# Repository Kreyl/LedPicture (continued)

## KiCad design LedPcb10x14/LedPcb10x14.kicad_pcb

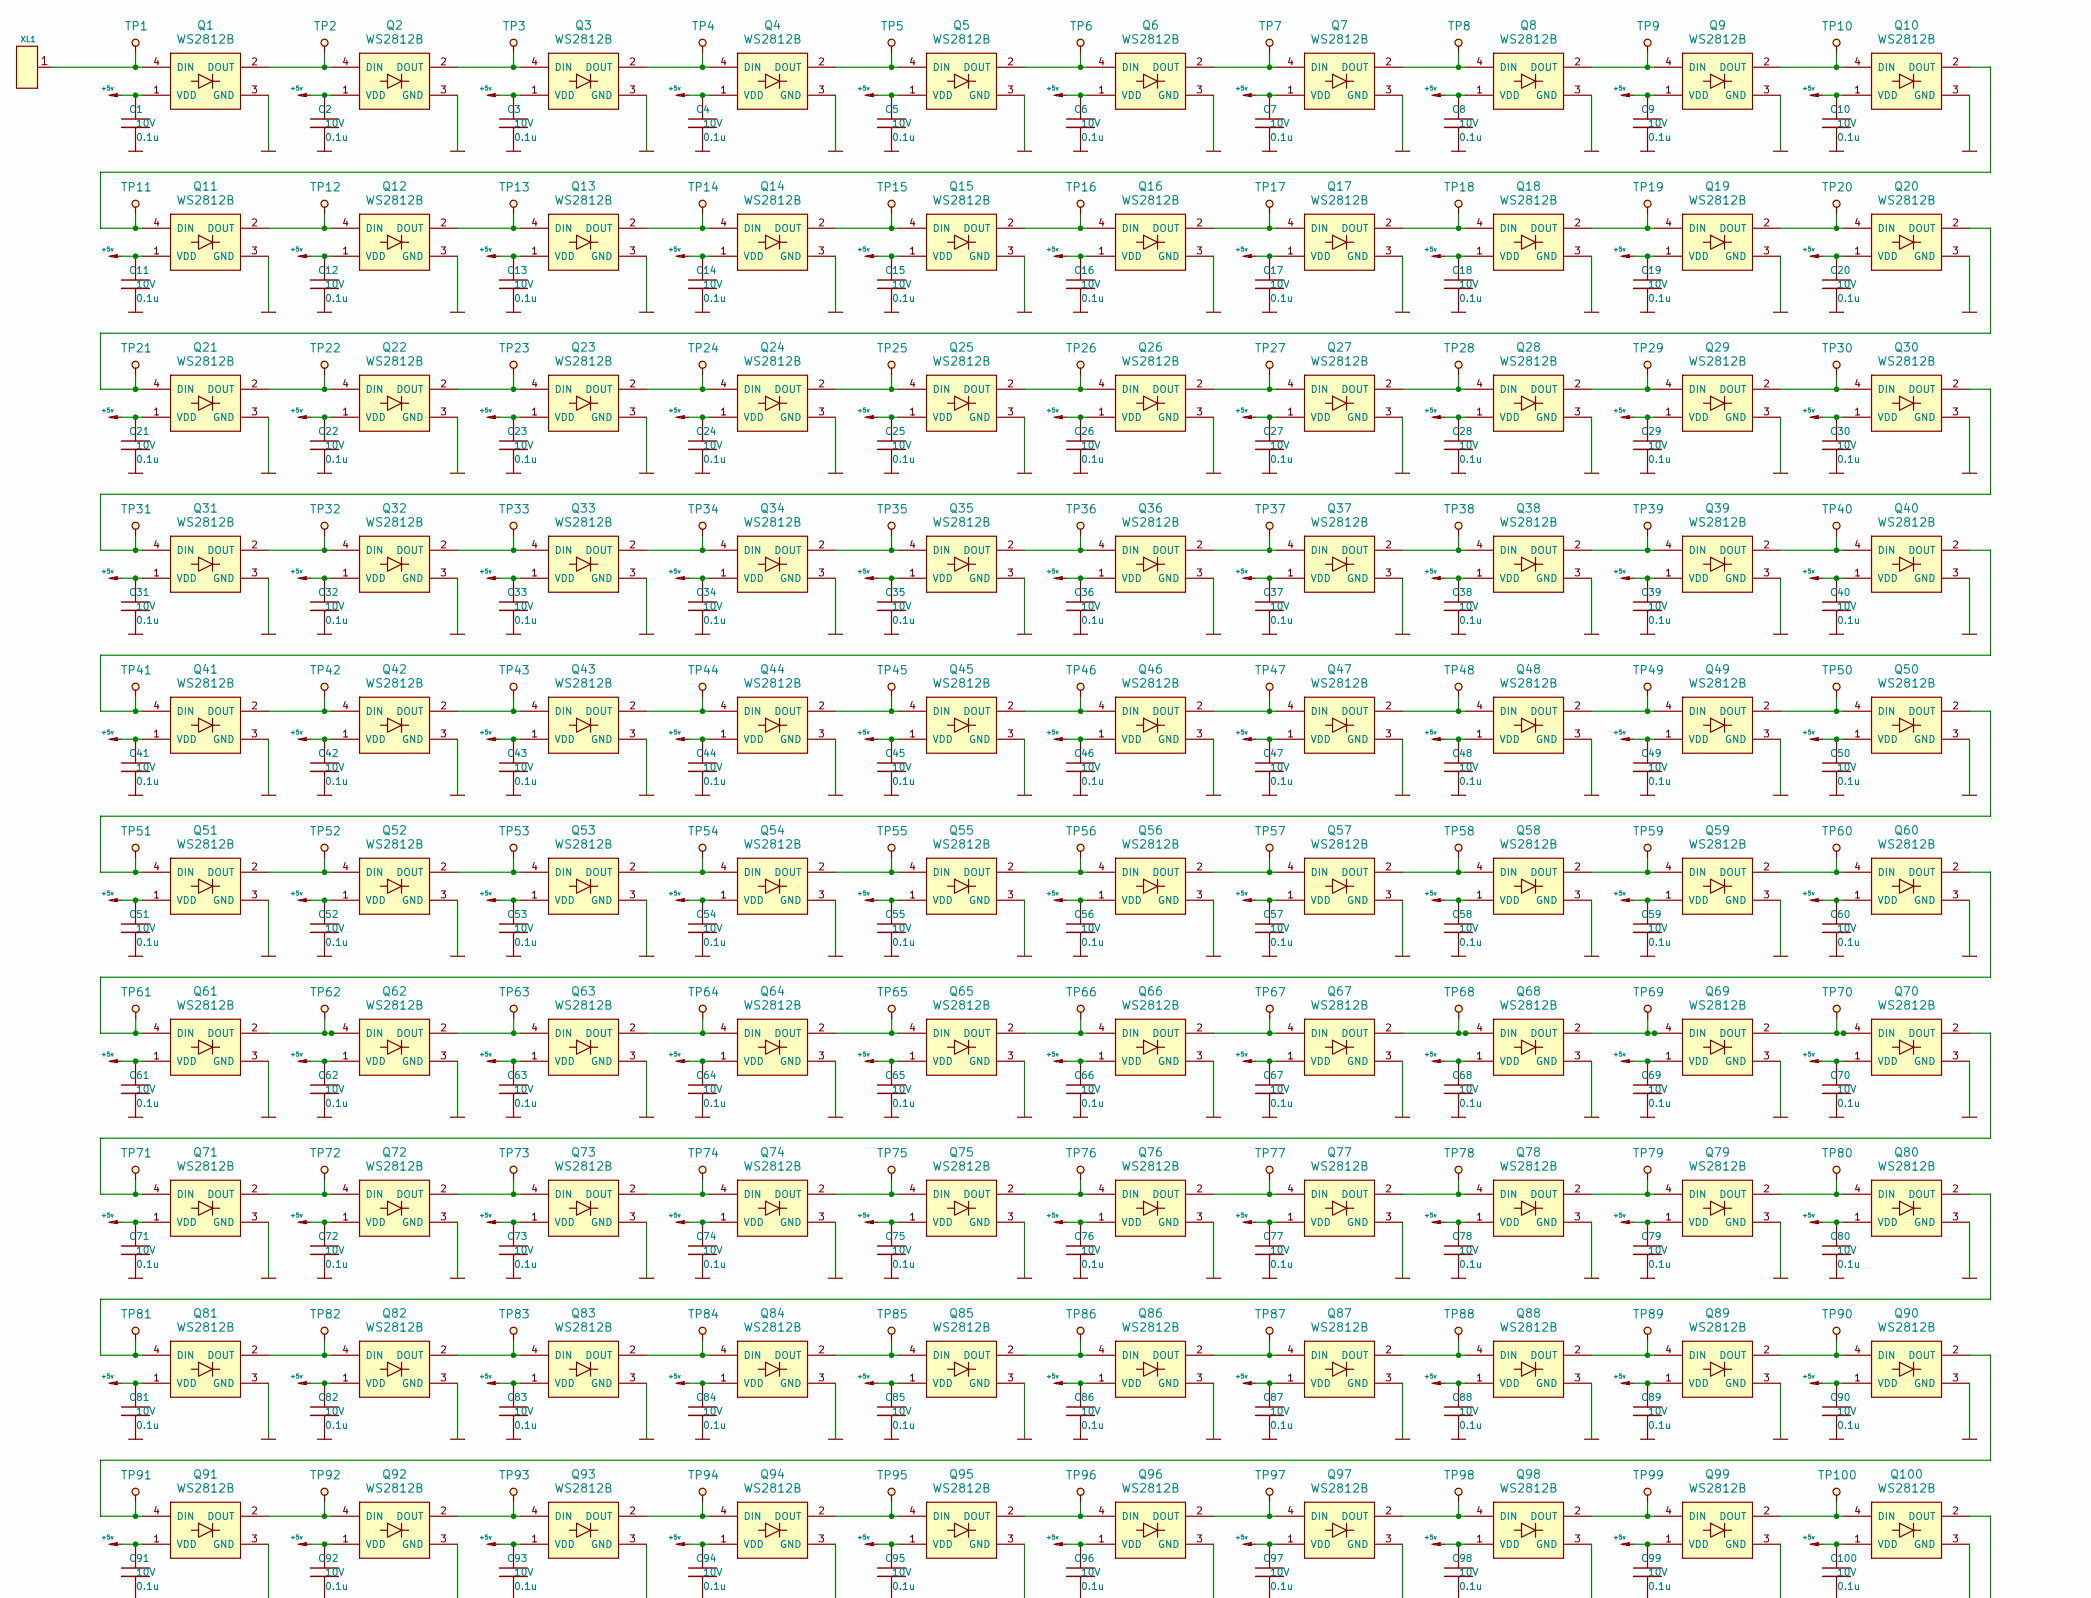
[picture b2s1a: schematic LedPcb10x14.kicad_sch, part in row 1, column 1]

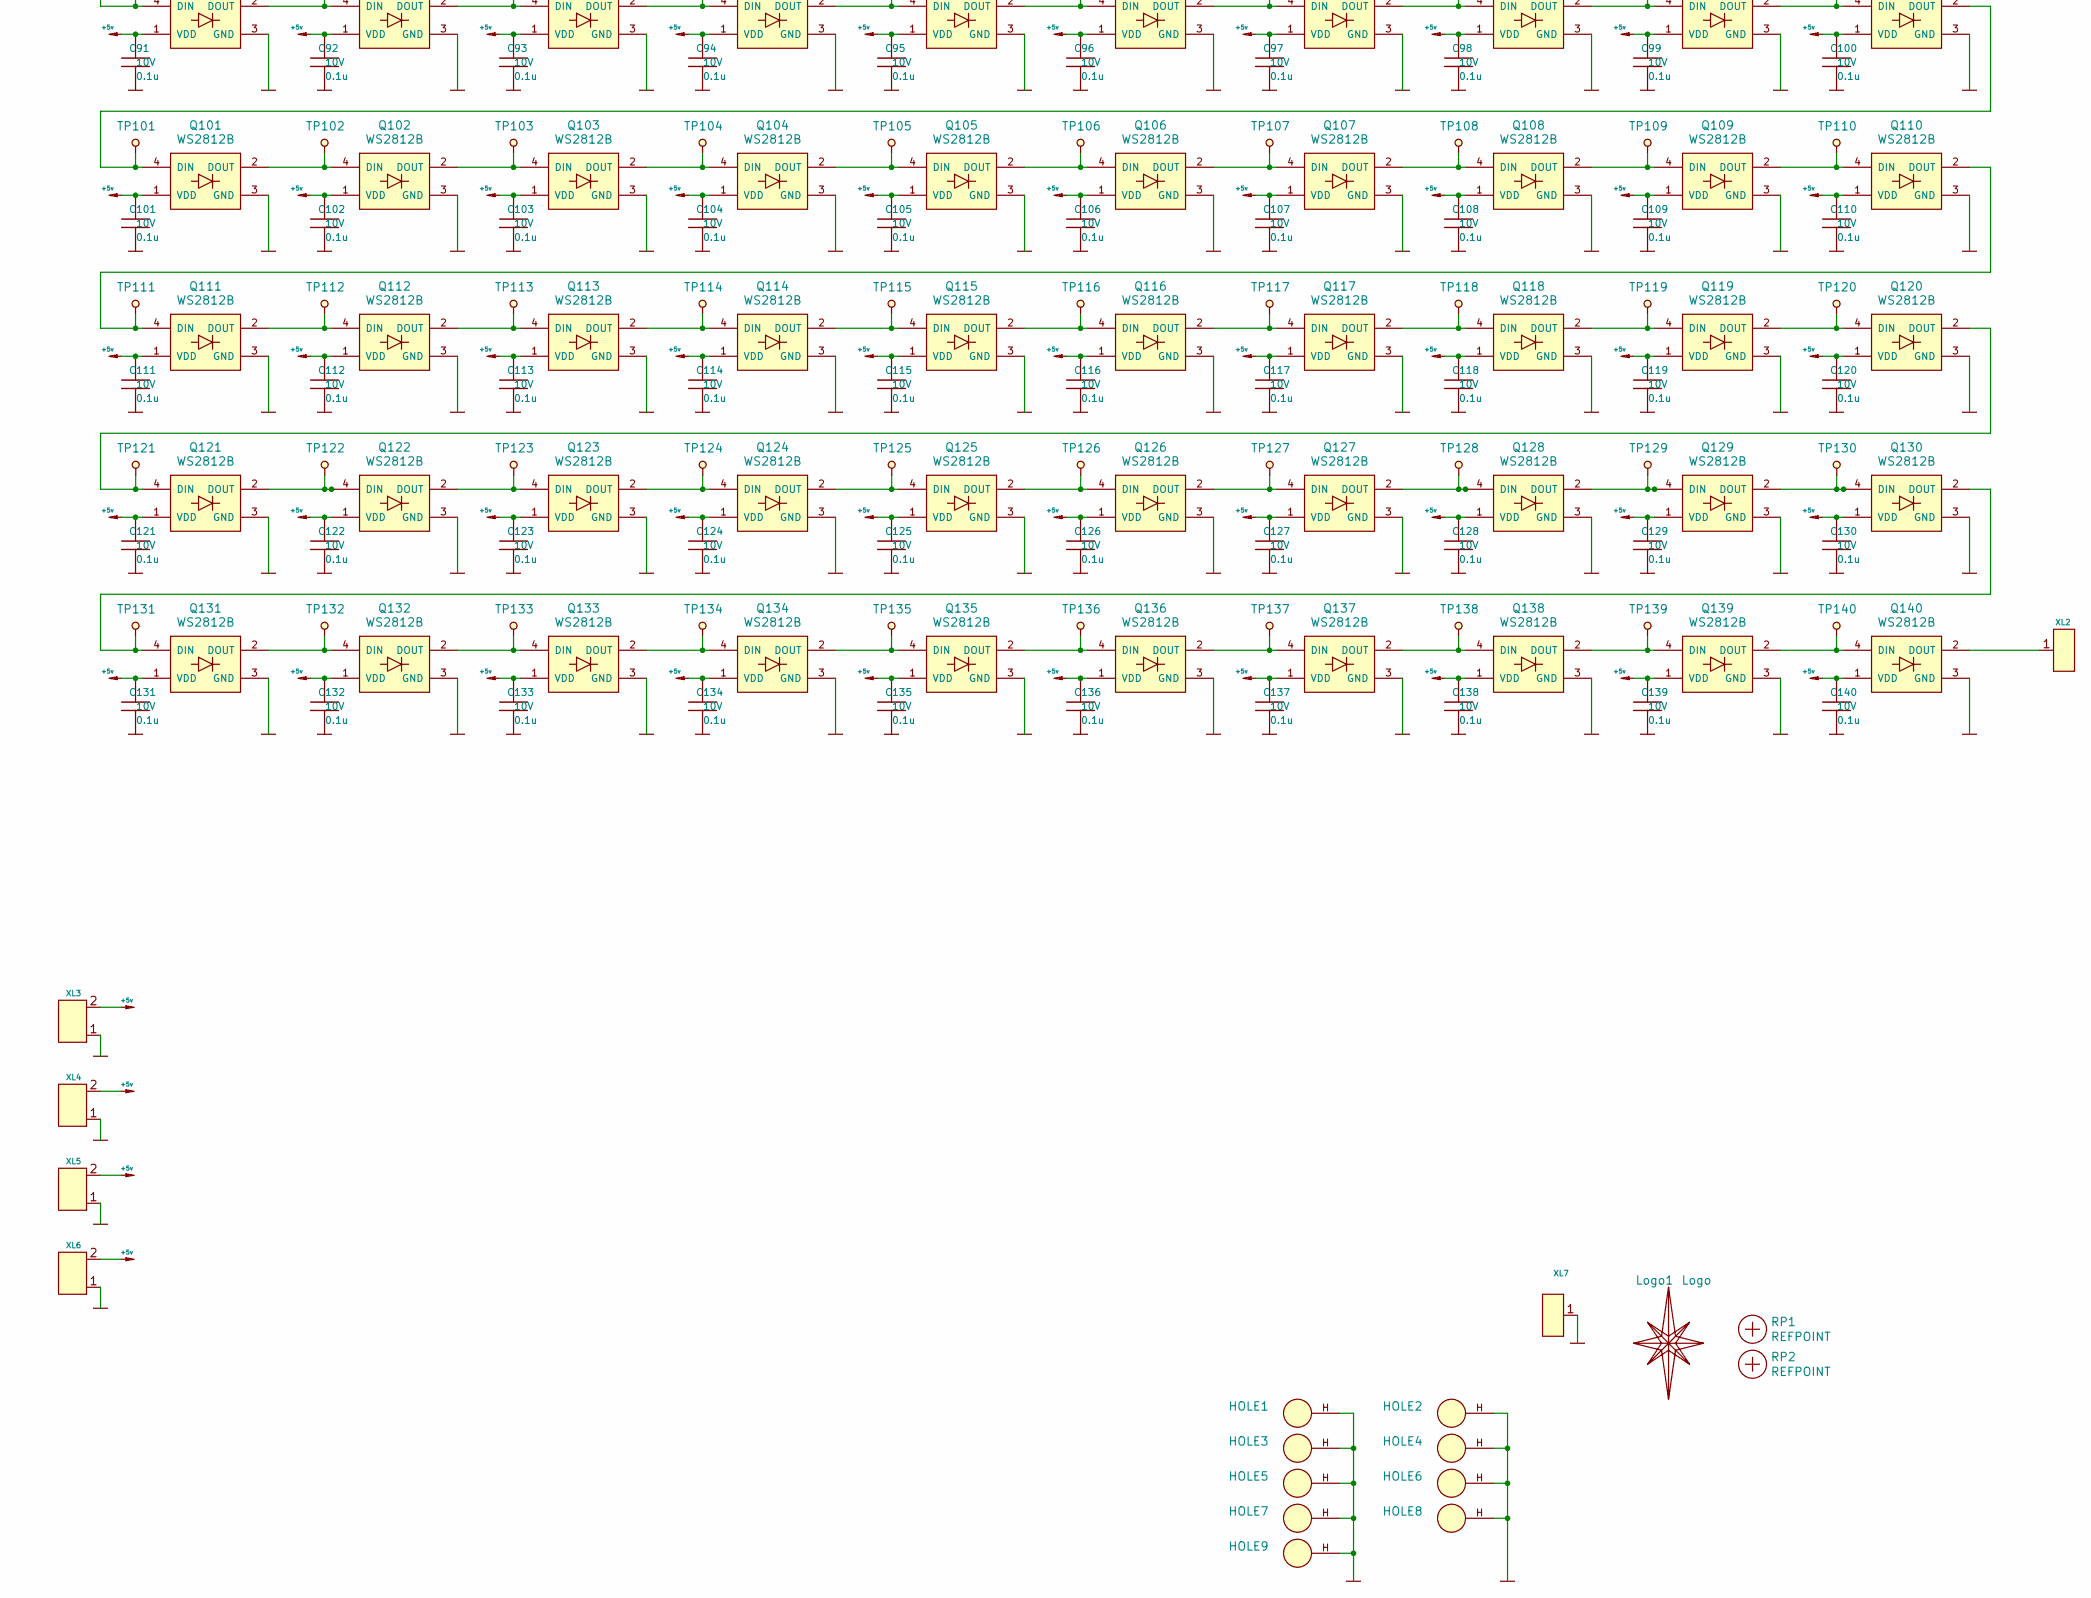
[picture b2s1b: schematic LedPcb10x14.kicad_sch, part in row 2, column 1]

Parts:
C1, C2, C3, C4, C5, C6, C7, C8, C9, C10, C11, C12, C13, C14, C15, C16, C17, C18, C19, C20, C21, C22, C23, C24, C25, C26, C27, C28, C29, C30, C31, C32, C33, C34, C35, C36, C37, C38, C39, C40, C41, C42, C43, C44, C45, C46, C47, C48, C49, C50, C51, C52, C53, C54, C55, C56, C57, C58, C59, C60, C61, C62, C63, C64, C65, C66, C67, C68, C69, C70, C71, C72, C73, C74, C75, C76, C77, C78, C79, C80, C81, C82, C83, C84, C85, C86, C87, C88, C89, C90, C91, C92, C93, C94, C95, C96, C97, C98, C99, C100, C101, C102, C103, C104, C105, C106, C107, C108, C109, C110, C111, C112, C113, C114, C115, C116, C117, C118, C119, C120, C121, C122, C123, C124, C125, C126, C127, C128, C129, C130, C131, C132, C133, C134, C135, C136, C137, C138, C139, C140: 0.1u; CAP_0603_Silks; Tolerance 20%; Voltage 10V
HOLE1, HOLE2, HOLE3, HOLE4, HOLE5, HOLE6, HOLE7, HOLE8, HOLE9: HOLE_METALLED; Hole2d2_out3d5mm
Logo1: Logo; Ostranna_12d7_10d1
Q1, Q2, Q3, Q4, Q5, Q6, Q7, Q8, Q9, Q10, Q11, Q12, Q13, Q14, Q15, Q16, Q17, Q18, Q19, Q20, Q21, Q22, Q23, Q24, Q25, Q26, Q27, Q28, Q29, Q30, Q31, Q32, Q33, Q34, Q35, Q36, Q37, Q38, Q39, Q40, Q41, Q42, Q43, Q44, Q45, Q46, Q47, Q48, Q49, Q50, Q51, Q52, Q53, Q54, Q55, Q56, Q57, Q58, Q59, Q60, Q61, Q62, Q63, Q64, Q65, Q66, Q67, Q68, Q69, Q70, Q71, Q72, Q73, Q74, Q75, Q76, Q77, Q78, Q79, Q80, Q81, Q82, Q83, Q84, Q85, Q86, Q87, Q88, Q89, Q90, Q91, Q92, Q93, Q94, Q95, Q96, Q97, Q98, Q99, Q100, Q101, Q102, Q103, Q104, Q105, Q106, Q107, Q108, Q109, Q110, Q111, Q112, Q113, Q114, Q115, Q116, Q117, Q118, Q119, Q120, Q121, Q122, Q123, Q124, Q125, Q126, Q127, Q128, Q129, Q130, Q131, Q132, Q133, Q134, Q135, Q136, Q137, Q138, Q139, Q140: WS2812B; LED_WS2812B
RP1, RP2: REFPOINT; REF_POINT_1MM
TP1, TP2, TP3, TP4, TP5, TP6, TP7, TP8, TP9, TP10, TP11, TP12, TP13, TP14, TP15, TP16, TP17, TP18, TP19, TP20, TP21, TP22, TP23, TP24, TP25, TP26, TP27, TP28, TP29, TP30, TP31, TP32, TP33, TP34, TP35, TP36, TP37, TP38, TP39, TP40, TP41, TP42, TP43, TP44, TP45, TP46, TP47, TP48, TP49, TP50, TP51, TP52, TP53, TP54, TP55, TP56, TP57, TP58, TP59, TP60, TP61, TP62, TP63, TP64, TP65, TP66, TP67, TP68, TP69, TP70, TP71, TP72, TP73, TP74, TP75, TP76, TP77, TP78, TP79, TP80, TP81, TP82, TP83, TP84, TP85, TP86, TP87, TP88, TP89, TP90, TP91, TP92, TP93, TP94, TP95, TP96, TP97, TP98, TP99, TP100, TP101, TP102, TP103, TP104, TP105, TP106, TP107, TP108, TP109, TP110, TP111, TP112, TP113, TP114, TP115, TP116, TP117, TP118, TP119, TP120, TP121, TP122, TP123, TP124, TP125, TP126, TP127, TP128, TP129, TP130, TP131, TP132, TP133, TP134, TP135, TP136, TP137, TP138, TP139, TP140: TESTPOINT; TESTPOINT_1MM
XL1, XL2: CONN_1; PLS-1Oval
XL3, XL4, XL5, XL6: CONN_2; TermiBlockHeader_508_x2_R
XL7: CONN_1; PLS-1Square

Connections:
+5v: C1.1, C2.1, C3.1, C4.1, C5.1, C6.1, C7.1, C8.1, C9.1, C10.1, C11.1, C12.1, C13.1, C14.1, C15.1, C16.1, C17.1, C18.1, C19.1, C20.1, C21.1, C22.1, C23.1, C24.1, C25.1, C26.1, C27.1, C28.1, C29.1, C30.1, C31.1, C32.1, C33.1, C34.1, C35.1, C36.1, C37.1, C38.1, C39.1, C40.1, C41.1, C42.1, C43.1, C44.1, C45.1, C46.1, C47.1, C48.1, C49.1, C50.1, C51.1, C52.1, C53.1, C54.1, C55.1, C56.1, C57.1, C58.1, C59.1, C60.1, C61.1, C62.1, C63.1, C64.1, C65.1, C66.1, C67.1, C68.1, C69.1, C70.1, C71.1, C72.1, C73.1, C74.1, C75.1, C76.1, C77.1, C78.1, C79.1, C80.1, C81.1, C82.1, C83.1, C84.1, C85.1, C86.1, C87.1, C88.1, C89.1, C90.1, C91.1, C92.1, C93.1, C94.1, C95.1, C96.1, C97.1, C98.1, C99.1, C100.1, C101.1, C102.1, C103.1, C104.1, C105.1, C106.1, C107.1, C108.1, C109.1, C110.1, C111.1, C112.1, C113.1, C114.1, C115.1, C116.1, C117.1, C118.1, C119.1, C120.1, C121.1, C122.1, C123.1, C124.1, C125.1, C126.1, C127.1, C128.1, C129.1, C130.1, C131.1, C132.1, C133.1, C134.1, C135.1, C136.1, C137.1, C138.1, C139.1, C140.1, Q1.1 (VDD), Q2.1 (VDD), Q3.1 (VDD), Q4.1 (VDD), Q5.1 (VDD), Q6.1 (VDD), Q7.1 (VDD), Q8.1 (VDD), Q9.1 (VDD), Q10.1 (VDD), Q11.1 (VDD), Q12.1 (VDD), Q13.1 (VDD), Q14.1 (VDD), Q15.1 (VDD), Q16.1 (VDD), Q17.1 (VDD), Q18.1 (VDD), Q19.1 (VDD), Q20.1 (VDD), Q21.1 (VDD), Q22.1 (VDD), Q23.1 (VDD), Q24.1 (VDD), Q25.1 (VDD), Q26.1 (VDD), Q27.1 (VDD), Q28.1 (VDD), Q29.1 (VDD), Q30.1 (VDD), Q31.1 (VDD), Q32.1 (VDD), Q33.1 (VDD), Q34.1 (VDD), Q35.1 (VDD), Q36.1 (VDD), Q37.1 (VDD), Q38.1 (VDD), Q39.1 (VDD), Q40.1 (VDD), Q41.1 (VDD), Q42.1 (VDD), Q43.1 (VDD), Q44.1 (VDD), Q45.1 (VDD), Q46.1 (VDD), Q47.1 (VDD), Q48.1 (VDD), Q49.1 (VDD), Q50.1 (VDD), Q51.1 (VDD), Q52.1 (VDD), Q53.1 (VDD), Q54.1 (VDD), Q55.1 (VDD), Q56.1 (VDD), Q57.1 (VDD), Q58.1 (VDD), Q59.1 (VDD), Q60.1 (VDD), Q61.1 (VDD), Q62.1 (VDD), Q63.1 (VDD), Q64.1 (VDD), Q65.1 (VDD), Q66.1 (VDD), Q67.1 (VDD), Q68.1 (VDD), Q69.1 (VDD), Q70.1 (VDD), Q71.1 (VDD), Q72.1 (VDD), Q73.1 (VDD), Q74.1 (VDD), Q75.1 (VDD), Q76.1 (VDD), Q77.1 (VDD), Q78.1 (VDD), Q79.1 (VDD), Q80.1 (VDD), Q81.1 (VDD), Q82.1 (VDD), Q83.1 (VDD), Q84.1 (VDD), Q85.1 (VDD), Q86.1 (VDD), Q87.1 (VDD), Q88.1 (VDD), Q89.1 (VDD), Q90.1 (VDD), Q91.1 (VDD), Q92.1 (VDD), Q93.1 (VDD), Q94.1 (VDD), Q95.1 (VDD), Q96.1 (VDD), Q97.1 (VDD), Q98.1 (VDD), Q99.1 (VDD), Q100.1 (VDD), Q101.1 (VDD), Q102.1 (VDD), Q103.1 (VDD), Q104.1 (VDD), Q105.1 (VDD), Q106.1 (VDD), Q107.1 (VDD), Q108.1 (VDD), Q109.1 (VDD), Q110.1 (VDD), Q111.1 (VDD), Q112.1 (VDD), Q113.1 (VDD), Q114.1 (VDD), Q115.1 (VDD), Q116.1 (VDD), Q117.1 (VDD), Q118.1 (VDD), Q119.1 (VDD), Q120.1 (VDD), Q121.1 (VDD), Q122.1 (VDD), Q123.1 (VDD), Q124.1 (VDD), Q125.1 (VDD), Q126.1 (VDD), Q127.1 (VDD), Q128.1 (VDD), Q129.1 (VDD), Q130.1 (VDD), Q131.1 (VDD), Q132.1 (VDD), Q133.1 (VDD), Q134.1 (VDD), Q135.1 (VDD), Q136.1 (VDD), Q137.1 (VDD), Q138.1 (VDD), Q139.1 (VDD), Q140.1 (VDD), XL3.2 (PM), XL4.2 (PM), XL5.2 (PM), XL6.2 (PM)
GND: C1.2, C2.2, C3.2, C4.2, C5.2, C6.2, C7.2, C8.2, C9.2, C10.2, C11.2, C12.2, C13.2, C14.2, C15.2, C16.2, C17.2, C18.2, C19.2, C20.2, C21.2, C22.2, C23.2, C24.2, C25.2, C26.2, C27.2, C28.2, C29.2, C30.2, C31.2, C32.2, C33.2, C34.2, C35.2, C36.2, C37.2, C38.2, C39.2, C40.2, C41.2, C42.2, C43.2, C44.2, C45.2, C46.2, C47.2, C48.2, C49.2, C50.2, C51.2, C52.2, C53.2, C54.2, C55.2, C56.2, C57.2, C58.2, C59.2, C60.2, C61.2, C62.2, C63.2, C64.2, C65.2, C66.2, C67.2, C68.2, C69.2, C70.2, C71.2, C72.2, C73.2, C74.2, C75.2, C76.2, C77.2, C78.2, C79.2, C80.2, C81.2, C82.2, C83.2, C84.2, C85.2, C86.2, C87.2, C88.2, C89.2, C90.2, C91.2, C92.2, C93.2, C94.2, C95.2, C96.2, C97.2, C98.2, C99.2, C100.2, C101.2, C102.2, C103.2, C104.2, C105.2, C106.2, C107.2, C108.2, C109.2, C110.2, C111.2, C112.2, C113.2, C114.2, C115.2, C116.2, C117.2, C118.2, C119.2, C120.2, C121.2, C122.2, C123.2, C124.2, C125.2, C126.2, C127.2, C128.2, C129.2, C130.2, C131.2, C132.2, C133.2, C134.2, C135.2, C136.2, C137.2, C138.2, C139.2, C140.2, HOLE1.H, HOLE2.H, HOLE3.H, HOLE4.H, HOLE5.H, HOLE6.H, HOLE7.H, HOLE8.H, HOLE9.H, Q1.3 (GND), Q2.3 (GND), Q3.3 (GND), Q4.3 (GND), Q5.3 (GND), Q6.3 (GND), Q7.3 (GND), Q8.3 (GND), Q9.3 (GND), Q10.3 (GND), Q11.3 (GND), Q12.3 (GND), Q13.3 (GND), Q14.3 (GND), Q15.3 (GND), Q16.3 (GND), Q17.3 (GND), Q18.3 (GND), Q19.3 (GND), Q20.3 (GND), Q21.3 (GND), Q22.3 (GND), Q23.3 (GND), Q24.3 (GND), Q25.3 (GND), Q26.3 (GND), Q27.3 (GND), Q28.3 (GND), Q29.3 (GND), Q30.3 (GND), Q31.3 (GND), Q32.3 (GND), Q33.3 (GND), Q34.3 (GND), Q35.3 (GND), Q36.3 (GND), Q37.3 (GND), Q38.3 (GND), Q39.3 (GND), Q40.3 (GND), Q41.3 (GND), Q42.3 (GND), Q43.3 (GND), Q44.3 (GND), Q45.3 (GND), Q46.3 (GND), Q47.3 (GND), Q48.3 (GND), Q49.3 (GND), Q50.3 (GND), Q51.3 (GND), Q52.3 (GND), Q53.3 (GND), Q54.3 (GND), Q55.3 (GND), Q56.3 (GND), Q57.3 (GND), Q58.3 (GND), Q59.3 (GND), Q60.3 (GND), Q61.3 (GND), Q62.3 (GND), Q63.3 (GND), Q64.3 (GND), Q65.3 (GND), Q66.3 (GND), Q67.3 (GND), Q68.3 (GND), Q69.3 (GND), Q70.3 (GND), Q71.3 (GND), Q72.3 (GND), Q73.3 (GND), Q74.3 (GND), Q75.3 (GND), Q76.3 (GND), Q77.3 (GND), Q78.3 (GND), Q79.3 (GND), Q80.3 (GND), Q81.3 (GND), Q82.3 (GND), Q83.3 (GND), Q84.3 (GND), Q85.3 (GND), Q86.3 (GND), Q87.3 (GND), Q88.3 (GND), Q89.3 (GND), Q90.3 (GND), Q91.3 (GND), Q92.3 (GND), Q93.3 (GND), Q94.3 (GND), Q95.3 (GND), Q96.3 (GND), Q97.3 (GND), Q98.3 (GND), Q99.3 (GND), Q100.3 (GND), Q101.3 (GND), Q102.3 (GND), Q103.3 (GND), Q104.3 (GND), Q105.3 (GND), Q106.3 (GND), Q107.3 (GND), Q108.3 (GND), Q109.3 (GND), Q110.3 (GND), Q111.3 (GND), Q112.3 (GND), Q113.3 (GND), Q114.3 (GND), Q115.3 (GND), Q116.3 (GND), Q117.3 (GND), Q118.3 (GND), Q119.3 (GND), Q120.3 (GND), Q121.3 (GND), Q122.3 (GND), Q123.3 (GND), Q124.3 (GND), Q125.3 (GND), Q126.3 (GND), Q127.3 (GND), Q128.3 (GND), Q129.3 (GND), Q130.3 (GND), Q131.3 (GND), Q132.3 (GND), Q133.3 (GND), Q134.3 (GND), Q135.3 (GND), Q136.3 (GND), Q137.3 (GND), Q138.3 (GND), Q139.3 (GND), Q140.3 (GND), XL3.1, XL4.1, XL5.1, XL6.1, XL7.1
unnamed: Q1.2 (DOUT), Q2.4 (DIN), TP2.1
unnamed: Q1.4 (DIN), TP1.1, XL1.1
unnamed: Q2.2 (DOUT), Q3.4 (DIN), TP3.1
unnamed: Q3.2 (DOUT), Q4.4 (DIN), TP4.1
unnamed: Q4.2 (DOUT), Q5.4 (DIN), TP5.1
unnamed: Q5.2 (DOUT), Q6.4 (DIN), TP6.1
unnamed: Q6.2 (DOUT), Q7.4 (DIN), TP7.1
unnamed: Q7.2 (DOUT), Q8.4 (DIN), TP8.1
unnamed: Q8.2 (DOUT), Q9.4 (DIN), TP9.1
unnamed: Q10.2 (DOUT), Q11.4 (DIN), TP11.1
unnamed: Q9.2 (DOUT), Q10.4 (DIN), TP10.1
unnamed: Q11.2 (DOUT), Q12.4 (DIN), TP12.1
unnamed: Q12.2 (DOUT), Q13.4 (DIN), TP13.1
unnamed: Q13.2 (DOUT), Q14.4 (DIN), TP14.1
unnamed: Q14.2 (DOUT), Q15.4 (DIN), TP15.1
unnamed: Q15.2 (DOUT), Q16.4 (DIN), TP16.1
unnamed: Q16.2 (DOUT), Q17.4 (DIN), TP17.1
unnamed: Q17.2 (DOUT), Q18.4 (DIN), TP18.1
unnamed: Q18.2 (DOUT), Q19.4 (DIN), TP19.1
unnamed: Q19.2 (DOUT), Q20.4 (DIN), TP20.1
unnamed: Q20.2 (DOUT), Q21.4 (DIN), TP21.1
unnamed: Q21.2 (DOUT), Q22.4 (DIN), TP22.1
unnamed: Q22.2 (DOUT), Q23.4 (DIN), TP23.1
unnamed: Q23.2 (DOUT), Q24.4 (DIN), TP24.1
unnamed: Q24.2 (DOUT), Q25.4 (DIN), TP25.1
unnamed: Q25.2 (DOUT), Q26.4 (DIN), TP26.1
unnamed: Q26.2 (DOUT), Q27.4 (DIN), TP27.1
unnamed: Q27.2 (DOUT), Q28.4 (DIN), TP28.1
unnamed: Q28.2 (DOUT), Q29.4 (DIN), TP29.1
unnamed: Q29.2 (DOUT), Q30.4 (DIN), TP30.1
unnamed: Q30.2 (DOUT), Q31.4 (DIN), TP31.1
unnamed: Q31.2 (DOUT), Q32.4 (DIN), TP32.1
unnamed: Q32.2 (DOUT), Q33.4 (DIN), TP33.1
unnamed: Q33.2 (DOUT), Q34.4 (DIN), TP34.1
unnamed: Q34.2 (DOUT), Q35.4 (DIN), TP35.1
unnamed: Q35.2 (DOUT), Q36.4 (DIN), TP36.1
unnamed: Q36.2 (DOUT), Q37.4 (DIN), TP37.1
unnamed: Q37.2 (DOUT), Q38.4 (DIN), TP38.1
unnamed: Q38.2 (DOUT), Q39.4 (DIN), TP39.1
unnamed: Q39.2 (DOUT), Q40.4 (DIN), TP40.1
unnamed: Q40.2 (DOUT), Q41.4 (DIN), TP41.1
unnamed: Q41.2 (DOUT), Q42.4 (DIN), TP42.1
unnamed: Q42.2 (DOUT), Q43.4 (DIN), TP43.1
unnamed: Q43.2 (DOUT), Q44.4 (DIN), TP44.1
unnamed: Q44.2 (DOUT), Q45.4 (DIN), TP45.1
unnamed: Q45.2 (DOUT), Q46.4 (DIN), TP46.1
unnamed: Q46.2 (DOUT), Q47.4 (DIN), TP47.1
unnamed: Q47.2 (DOUT), Q48.4 (DIN), TP48.1
unnamed: Q48.2 (DOUT), Q49.4 (DIN), TP49.1
unnamed: Q49.2 (DOUT), Q50.4 (DIN), TP50.1
unnamed: Q50.2 (DOUT), Q51.4 (DIN), TP51.1
unnamed: Q51.2 (DOUT), Q52.4 (DIN), TP52.1
unnamed: Q52.2 (DOUT), Q53.4 (DIN), TP53.1
unnamed: Q53.2 (DOUT), Q54.4 (DIN), TP54.1
unnamed: Q54.2 (DOUT), Q55.4 (DIN), TP55.1
unnamed: Q55.2 (DOUT), Q56.4 (DIN), TP56.1
unnamed: Q56.2 (DOUT), Q57.4 (DIN), TP57.1
unnamed: Q57.2 (DOUT), Q58.4 (DIN), TP58.1
unnamed: Q58.2 (DOUT), Q59.4 (DIN), TP59.1
unnamed: Q59.2 (DOUT), Q60.4 (DIN), TP60.1
unnamed: Q60.2 (DOUT), Q61.4 (DIN), TP61.1
unnamed: Q61.2 (DOUT), Q62.4 (DIN), TP62.1
unnamed: Q62.2 (DOUT), Q63.4 (DIN), TP63.1
unnamed: Q63.2 (DOUT), Q64.4 (DIN), TP64.1
unnamed: Q64.2 (DOUT), Q65.4 (DIN), TP65.1
unnamed: Q65.2 (DOUT), Q66.4 (DIN), TP66.1
unnamed: Q66.2 (DOUT), Q67.4 (DIN), TP67.1
unnamed: Q67.2 (DOUT), Q68.4 (DIN), TP68.1
unnamed: Q68.2 (DOUT), Q69.4 (DIN), TP69.1
unnamed: Q69.2 (DOUT), Q70.4 (DIN), TP70.1
unnamed: Q70.2 (DOUT), Q71.4 (DIN), TP71.1
unnamed: Q71.2 (DOUT), Q72.4 (DIN), TP72.1
unnamed: Q72.2 (DOUT), Q73.4 (DIN), TP73.1
unnamed: Q73.2 (DOUT), Q74.4 (DIN), TP74.1
unnamed: Q74.2 (DOUT), Q75.4 (DIN), TP75.1
unnamed: Q75.2 (DOUT), Q76.4 (DIN), TP76.1
unnamed: Q76.2 (DOUT), Q77.4 (DIN), TP77.1
unnamed: Q77.2 (DOUT), Q78.4 (DIN), TP78.1
unnamed: Q78.2 (DOUT), Q79.4 (DIN), TP79.1
unnamed: Q79.2 (DOUT), Q80.4 (DIN), TP80.1
unnamed: Q80.2 (DOUT), Q81.4 (DIN), TP81.1
unnamed: Q81.2 (DOUT), Q82.4 (DIN), TP82.1
unnamed: Q82.2 (DOUT), Q83.4 (DIN), TP83.1
unnamed: Q83.2 (DOUT), Q84.4 (DIN), TP84.1
unnamed: Q84.2 (DOUT), Q85.4 (DIN), TP85.1
unnamed: Q85.2 (DOUT), Q86.4 (DIN), TP86.1
unnamed: Q86.2 (DOUT), Q87.4 (DIN), TP87.1
unnamed: Q87.2 (DOUT), Q88.4 (DIN), TP88.1
unnamed: Q88.2 (DOUT), Q89.4 (DIN), TP89.1
unnamed: Q89.2 (DOUT), Q90.4 (DIN), TP90.1
unnamed: Q90.2 (DOUT), Q91.4 (DIN), TP91.1
unnamed: Q91.2 (DOUT), Q92.4 (DIN), TP92.1
unnamed: Q92.2 (DOUT), Q93.4 (DIN), TP93.1
unnamed: Q93.2 (DOUT), Q94.4 (DIN), TP94.1
unnamed: Q94.2 (DOUT), Q95.4 (DIN), TP95.1
unnamed: Q95.2 (DOUT), Q96.4 (DIN), TP96.1
unnamed: Q96.2 (DOUT), Q97.4 (DIN), TP97.1
unnamed: Q97.2 (DOUT), Q98.4 (DIN), TP98.1
unnamed: Q98.2 (DOUT), Q99.4 (DIN), TP99.1
unnamed: Q100.2 (DOUT), Q101.4 (DIN), TP101.1
unnamed: Q99.2 (DOUT), Q100.4 (DIN), TP100.1
unnamed: Q101.2 (DOUT), Q102.4 (DIN), TP102.1
unnamed: Q102.2 (DOUT), Q103.4 (DIN), TP103.1
unnamed: Q103.2 (DOUT), Q104.4 (DIN), TP104.1
unnamed: Q105.2 (DOUT), Q106.4 (DIN), TP106.1
unnamed: Q106.2 (DOUT), Q107.4 (DIN), TP107.1
unnamed: Q107.2 (DOUT), Q108.4 (DIN), TP108.1
unnamed: Q108.2 (DOUT), Q109.4 (DIN), TP109.1
unnamed: Q109.2 (DOUT), Q110.4 (DIN), TP110.1
unnamed: Q110.2 (DOUT), Q111.4 (DIN), TP111.1
unnamed: Q111.2 (DOUT), Q112.4 (DIN), TP112.1
unnamed: Q112.2 (DOUT), Q113.4 (DIN), TP113.1
unnamed: Q113.2 (DOUT), Q114.4 (DIN), TP114.1
unnamed: Q114.2 (DOUT), Q115.4 (DIN), TP115.1
unnamed: Q115.2 (DOUT), Q116.4 (DIN), TP116.1
unnamed: Q116.2 (DOUT), Q117.4 (DIN), TP117.1
unnamed: Q117.2 (DOUT), Q118.4 (DIN), TP118.1
unnamed: Q118.2 (DOUT), Q119.4 (DIN), TP119.1
unnamed: Q119.2 (DOUT), Q120.4 (DIN), TP120.1
unnamed: Q120.2 (DOUT), Q121.4 (DIN), TP121.1
unnamed: Q121.2 (DOUT), Q122.4 (DIN), TP122.1
unnamed: Q122.2 (DOUT), Q123.4 (DIN), TP123.1
unnamed: Q123.2 (DOUT), Q124.4 (DIN), TP124.1
unnamed: Q124.2 (DOUT), Q125.4 (DIN), TP125.1
unnamed: Q125.2 (DOUT), Q126.4 (DIN), TP126.1
unnamed: Q126.2 (DOUT), Q127.4 (DIN), TP127.1
unnamed: Q127.2 (DOUT), Q128.4 (DIN), TP128.1
unnamed: Q128.2 (DOUT), Q129.4 (DIN), TP129.1
unnamed: Q129.2 (DOUT), Q130.4 (DIN), TP130.1
unnamed: Q130.2 (DOUT), Q131.4 (DIN), TP131.1
unnamed: Q131.2 (DOUT), Q132.4 (DIN), TP132.1
unnamed: Q132.2 (DOUT), Q133.4 (DIN), TP133.1
unnamed: Q133.2 (DOUT), Q134.4 (DIN), TP134.1
unnamed: Q134.2 (DOUT), Q135.4 (DIN), TP135.1
unnamed: Q135.2 (DOUT), Q136.4 (DIN), TP136.1
unnamed: Q136.2 (DOUT), Q137.4 (DIN), TP137.1
unnamed: Q137.2 (DOUT), Q138.4 (DIN), TP138.1
unnamed: Q138.2 (DOUT), Q139.4 (DIN), TP139.1
unnamed: Q139.2 (DOUT), Q140.4 (DIN), TP140.1
unnamed: Q140.2 (DOUT), XL2.1
unnamed: Q104.2 (DOUT), Q105.4 (DIN), TP105.1

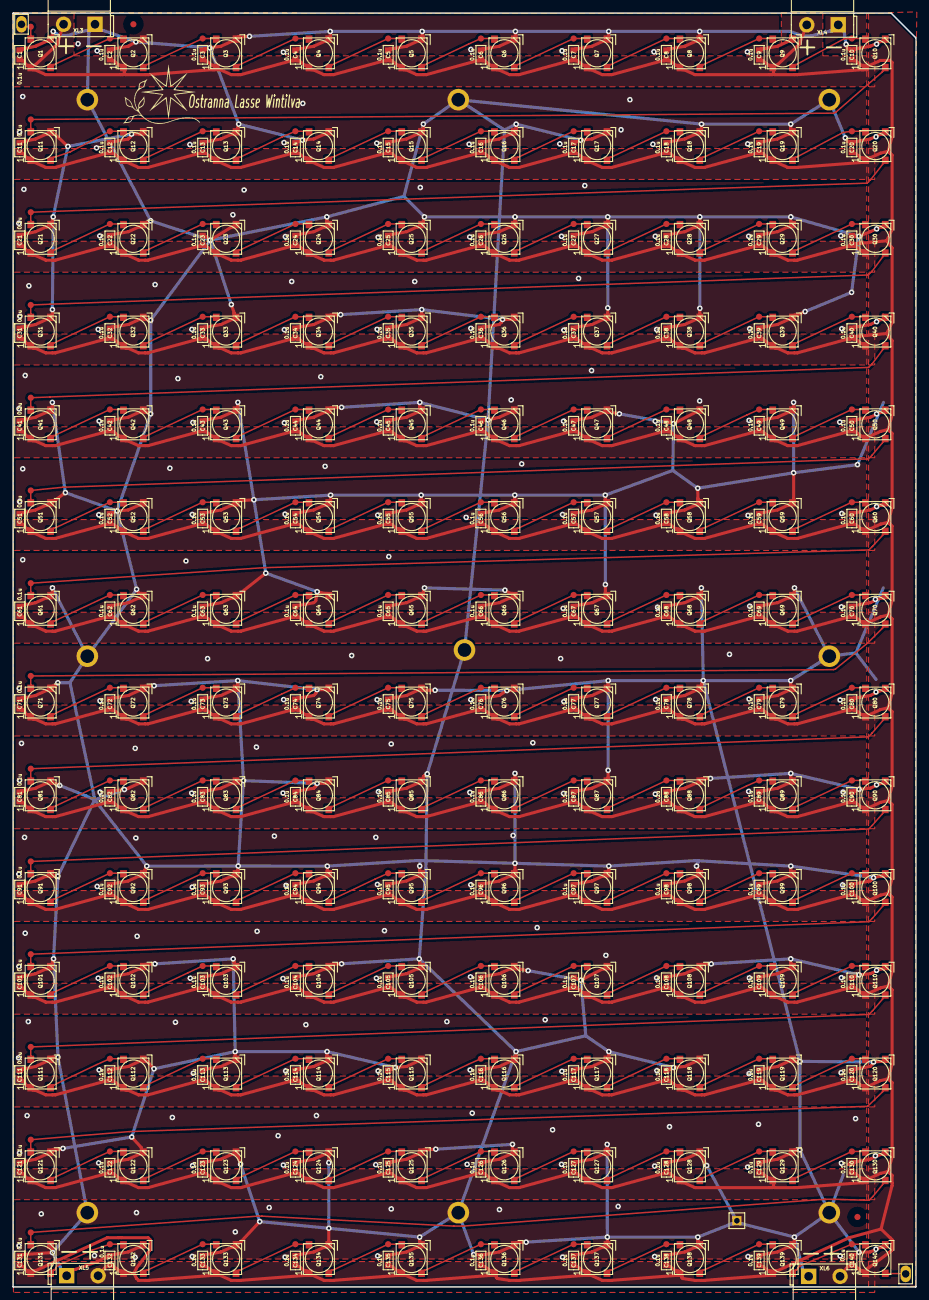
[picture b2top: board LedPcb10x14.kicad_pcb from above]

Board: 2 copper layers, 146.0 x 206.0 mm, 439 parts (0 on the bottom side), 143 nets.

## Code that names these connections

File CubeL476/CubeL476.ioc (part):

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Mcu.Name=STM32L476R(C-E-G)Tx
Mcu.Package=LQFP64
Mcu.UserName=STM32L476RCTx
PA0.Signal=GPIO_Input
PA1.Signal=GPIO_Input
PA10.Mode=Asynchronous
PA10.Signal=USART1_RX
PA11.Mode=Device_Only
PA11.Signal=USB_OTG_FS_DM
PA12.Mode=Device_Only
PA12.Signal=USB_OTG_FS_DP
PA13\ (JTMS-SWDIO).Mode=Serial_Wire
PA13\ (JTMS-SWDIO).Signal=SYS_JTMS-SWDIO
PA14\ (JTCK-SWCLK).Mode=Serial_Wire
PA14\ (JTCK-SWCLK).Signal=SYS_JTCK-SWCLK
PA2.Signal=GPIO_Input
PA3.Signal=GPIO_Input
PA4.Signal=GPIO_Output
PA5.Mode=Full_Duplex_Master
PA5.Signal=SPI1_SCK
PA6.Mode=Full_Duplex_Master
PA6.Signal=SPI1_MISO
PA7.Mode=Full_Duplex_Master
PA7.Signal=SPI1_MOSI
PA9.Mode=Asynchronous
PA9.Signal=USART1_TX
PB13.Mode=TX_Only_Simplex_Unidirect_Master
PB13.Signal=SPI2_SCK
PB15.Mode=TX_Only_Simplex_Unidirect_Master
PB15.Signal=SPI2_MOSI
PB4\ (NJTRST).Signal=S_TIM3_CH1
PB5.Signal=S_TIM3_CH2
PB9.Signal=S_TIM17_CH1
PC0.Mode=I2C
PC0.Signal=I2C3_SCL
PC1.Mode=I2C
PC1.Signal=I2C3_SDA
PC10.Mode=TX_Only_Simplex_Unidirect_Master
PC10.Signal=SPI3_SCK
PC12.Mode=TX_Only_Simplex_Unidirect_Master
PC12.Signal=SPI3_MOSI
PC14-OSC32_IN\ (PC14).Signal=GPIO_Input
PC4.Signal=GPIO_Input
PC5.Signal=GPIO_Input
PH0-OSC_IN\ (PH0).Mode=HSE-External-Oscillator
PH0-OSC_IN\ (PH0).Signal=RCC_OSC_IN
PH1-OSC_OUT\ (PH1).Mode=HSE-External-Oscillator
PH1-OSC_OUT\ (PH1).Signal=RCC_OSC_OUT
RCC.HSE_VALUE=8000000
board=custom

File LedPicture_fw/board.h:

/*
 * board.h
 *
 *  Created on: 05 08 2018
 *      Author: Kreyl
 */

#pragma once

// ==== General ====
#define APP_NAME            "LedPicture"

// Version of PCB
#define PCB_VER                 1

// MCU type as defined in the ST header.
#define STM32L476xx

// Freq of external crystal if any. Leave it here even if not used.
#define CRYSTAL_FREQ_HZ         12000000

// OS timer settings
#define STM32_ST_IRQ_PRIORITY   2
#define STM32_ST_USE_TIMER      5
#define SYS_TIM_CLK             (Clk.APB1FreqHz)    // Timer 5 is clocked by APB1

//  Periphery
#define I2C1_ENABLED            FALSE
#define I2C2_ENABLED            FALSE
#define I2C3_ENABLED            TRUE

#define ADC_REQUIRED            FALSE
#define STM32_DMA_REQUIRED      TRUE    // Leave this macro name for OS

#if 1 // ========================== GPIO =======================================
// EXTI
#define INDIVIDUAL_EXTI_IRQ_REQUIRED    FALSE

// UART
#define UART_GPIO       GPIOA
#define UART_TX_PIN     9
#define UART_RX_PIN     10

// Different pins
#define PWR_EN          GPIOD, 2, omPushPull

// LED
#define LED_PIN         { GPIOB, 9, TIM17, 1, invNotInverted, omPushPull, 255 }

// Neopixel LEDs
#define NPX_LED_CNT     560
#define NPX_SPI         SPI2
#define NPX_GPIO        GPIOB
#define NPX_PIN         15
#define NPX_AF          AF5

#define NPX2_LED_CNT    25
#define NPX2_SPI        SPI3
#define NPX2_GPIO       GPIOC
#define NPX2_PIN        12
#define NPX2_AF         AF6

// ==== Lora ====
#define SX_SPI          SPI1
#define SX_SCK          GPIOA,  5, omPushPull, pudNone, AF5
#define SX_MISO         GPIOA,  6, omPushPull, pudNone, AF5
#define SX_MOSI         GPIOA,  7, omPushPull, pudNone, AF5
#define SX_NSS          GPIOA, 4
#define SX_NRESET       GPIOC, 3
#define SX_DIO0_GPIO    GPIOA
#define SX_DIO0_PIN     0
#define SX_DIO1_GPIO    GPIOA
#define SX_DIO1_PIN     1
#define SX_DIO2_GPIO    GPIOA
#define SX_DIO2_PIN     2
#define SX_DIO3_GPIO    GPIOA
#define SX_DIO3_PIN     3
#define SX_DIO4_GPIO    GPIOC
#define SX_DIO4_PIN     5
#define SX_DIO5_GPIO    GPIOC
#define SX_DIO5_PIN     4

// I2C
#define I2C1_GPIO       GPIOB
#define I2C1_SCL        6
#define I2C1_SDA        7
#define I2C2_GPIO       GPIOB
#define I2C2_SCL        10
#define I2C2_SDA        11
#define I2C3_GPIO       GPIOC
#define I2C3_SCL        0
#define I2C3_SDA        1
// I2C Alternate Function
#define I2C_AF          AF4

// USB
#define USB_DM          GPIOA, 11
#define USB_DP          GPIOA, 12
#define USB_AF          AF10
// USB detect
#define USB_DETECT_PIN  GPIOC, 9

#endif // GPIO

#if 1 // =========================== I2C =======================================
// i2cclkPCLK1, i2cclkSYSCLK, i2cclkHSI
#define I2C_CLK_SRC     i2cclkHSI
#define I2C_BAUDRATE_HZ 400000
#endif

#if ADC_REQUIRED // ======================= Inner ADC ==========================
// Clock divider: clock is generated from the APB2
#define ADC_CLK_DIVIDER		adcDiv2

// ADC channels
#define ADC_BATTERY_CHNL 	14
// ADC_VREFINT_CHNL
#define ADC_CHANNELS        { ADC_BATTERY_CHNL, ADC_VREFINT_CHNL }
#define ADC_CHANNEL_CNT     2   // Do not use countof(AdcChannels) as preprocessor does not know what is countof => cannot check
#define ADC_SAMPLE_TIME     ast24d5Cycles
#define ADC_OVERSAMPLING_RATIO  64   // 1 (no oversampling), 2, 4, 8, 16, 32, 64, 128, 256
#endif

#if 1 // =========================== DMA =======================================
// ==== Uart ====
// Remap is made automatically if required
#define UART_DMA_TX     STM32_DMA_STREAM_ID(2, 6)
#define UART_DMA_RX     STM32_DMA_STREAM_ID(2, 7)
#define UART_DMA_CHNL   2
#define UART_DMA_TX_MODE(Chnl) (STM32_DMA_CR_CHSEL(Chnl) | DMA_PRIORITY_LOW | STM32_DMA_CR_MSIZE_BYTE | STM32_DMA_CR_PSIZE_BYTE | STM32_DMA_CR_MINC | STM32_DMA_CR_DIR_M2P | STM32_DMA_CR_TCIE)
#define UART_DMA_RX_MODE(Chnl) (STM32_DMA_CR_CHSEL(Chnl) | DMA_PRIORITY_MEDIUM | STM32_DMA_CR_MSIZE_BYTE | STM32_DMA_CR_PSIZE_BYTE | STM32_DMA_CR_MINC | STM32_DMA_CR_DIR_P2M | STM32_DMA_CR_CIRC)

// ==== I2C ====
#define I2C_USE_DMA     TRUE
#define I2C1_DMA_TX     STM32_DMA_STREAM_ID(1, 6)
#define I2C1_DMA_RX     STM32_DMA_STREAM_ID(1, 7)
#define I2C1_DMA_CHNL   3
#define I2C2_DMA_TX     STM32_DMA_STREAM_ID(1, 4)
#define I2C2_DMA_RX     STM32_DMA_STREAM_ID(1, 5)
#define I2C2_DMA_CHNL   3
#define I2C3_DMA_TX     STM32_DMA_STREAM_ID(1, 2)
#define I2C3_DMA_RX     STM32_DMA_STREAM_ID(1, 3)
#define I2C3_DMA_CHNL   3

#define NPX_DMA         STM32_DMA_STREAM_ID(1, 5)
#define NPX_DMA_CHNL    1

#if ADC_REQUIRED
#define ADC_DMA         STM32_DMA1_STREAM1
#define ADC_DMA_MODE    STM32_DMA_CR_CHSEL(0) |   /* DMA1 Stream1 Channel0 */ \
                        DMA_PRIORITY_LOW | \
                        STM32_DMA_CR_MSIZE_HWORD | \
                        STM32_DMA_CR_PSIZE_HWORD | \
                        STM32_DMA_CR_MINC |       /* Memory pointer increase */ \
                        STM32_DMA_CR_DIR_P2M |    /* Direction is peripheral to memory */ \
                        STM32_DMA_CR_TCIE         /* Enable Transmission Complete IRQ */
#endif // ADC

#endif // DMA

#if 1 // ========================== USART ======================================
#define PRINTF_FLOAT_EN FALSE
#define UART_TXBUF_SZ   4096
#define UART_RXBUF_SZ   99
#define CMD_BUF_SZ      256

#define CMD_UART        USART1

#define CMD_UART_PARAMS \
    CMD_UART, UART_GPIO, UART_TX_PIN, UART_GPIO, UART_RX_PIN, \
    UART_DMA_TX, UART_DMA_RX, UART_DMA_TX_MODE(UART_DMA_CHNL), UART_DMA_RX_MODE(UART_DMA_CHNL), \
    uartclkHSI // Use independent clock

#endif

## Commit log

2021-07-11 PCBs sent to factory
2021-07-17 + OS works + Antenna tuned
2021-07-19 First LORA Rx ok
2021-07-19 + Fifo read ok
2021-07-19 * Fixed payload length in RX
2021-07-19 ExplicitHeader implemented
2021-07-20 WS2812 works ok
2021-07-20 + Py Control
2021-08-04 Release
